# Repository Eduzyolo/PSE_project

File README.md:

# PSE_project
This is the official repo for the PSE project 

# LICENSE
This repo is under CC BY-NC 4.0 license

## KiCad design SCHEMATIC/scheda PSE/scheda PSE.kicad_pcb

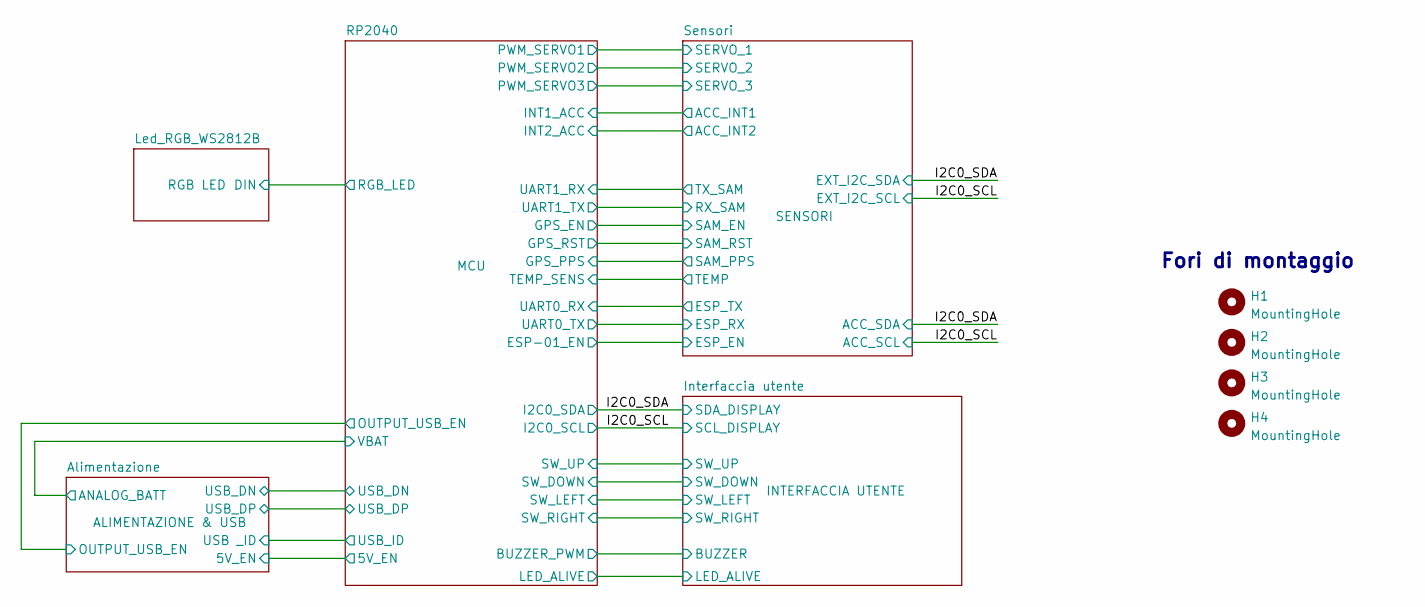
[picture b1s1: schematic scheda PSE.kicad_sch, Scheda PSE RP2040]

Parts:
H1, H2, H3, H4: MountingHole; MountingHole_3.2mm_M3_Pad_Via

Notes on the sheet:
Fori di montaggio

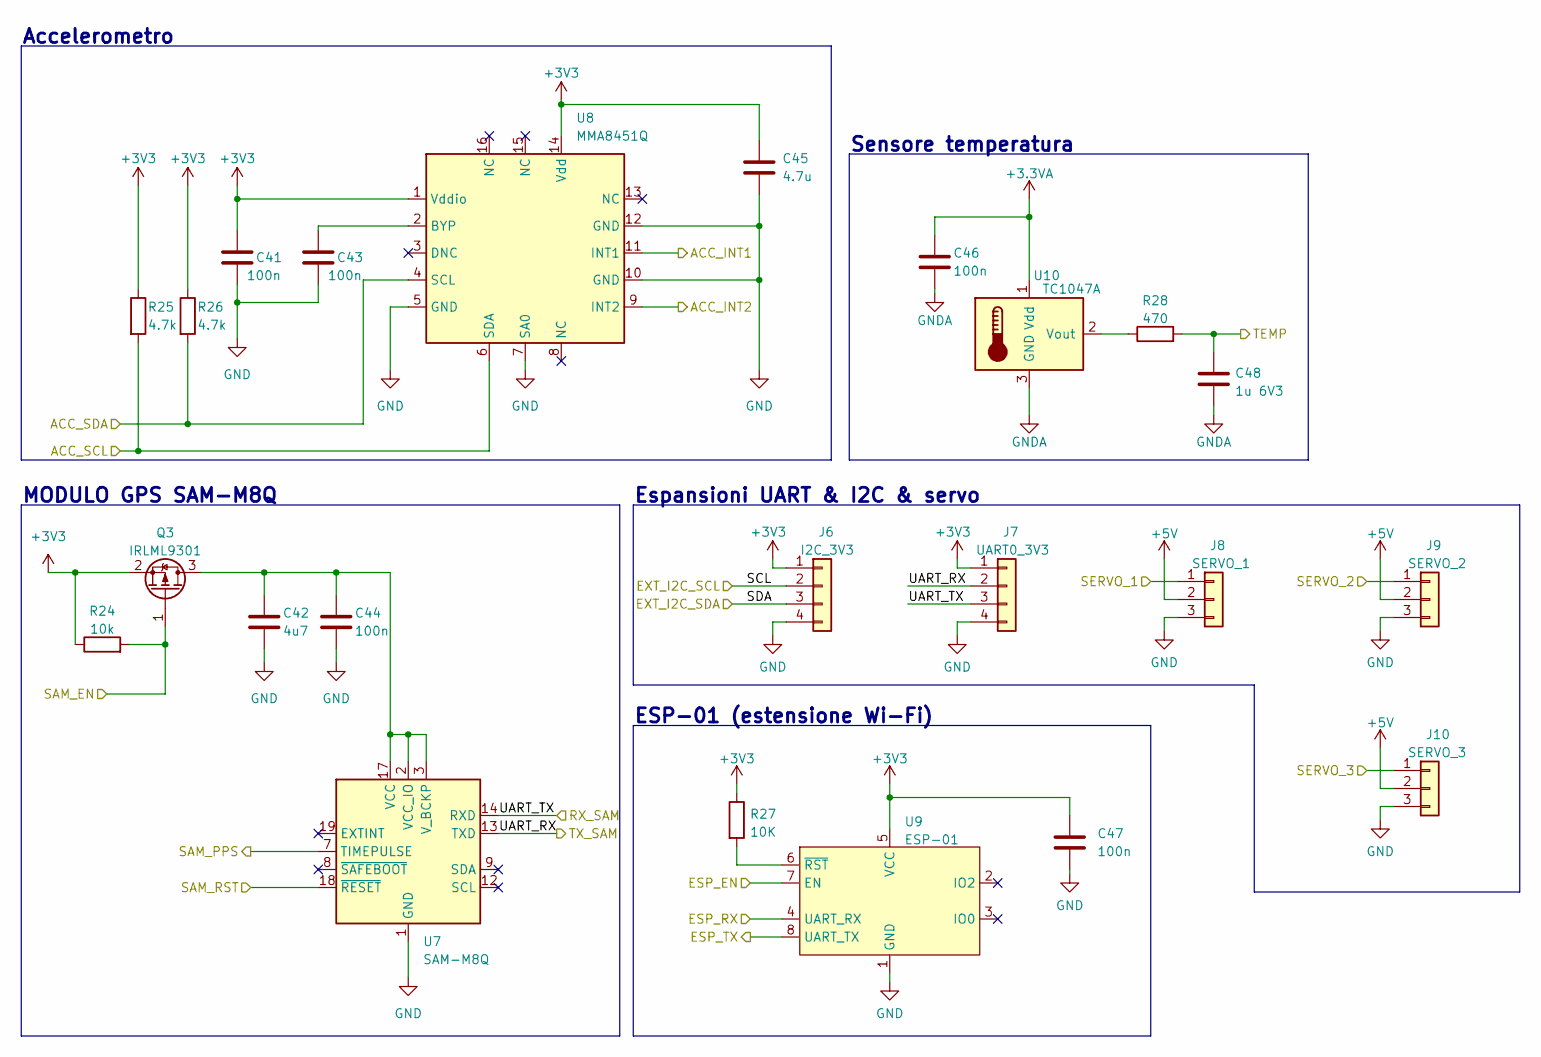
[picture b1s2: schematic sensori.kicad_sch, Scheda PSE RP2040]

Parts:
C41, C43, C44, C46, C47: 100n; C_0603_1608Metric
C42: 4u7; C_0603_1608Metric
C45: 4.7u; C_0603_1608Metric
C48: 1u 6V3; C_0603_1608Metric
J6: I2C_3V3; JST_XH_B4B-XH-A_1x04_P2.50mm_Vertical
J7: UART0_3V3; JST_XH_B4B-XH-A_1x04_P2.50mm_Vertical
J8: SERVO_1; PinHeader_1x03_P2.54mm_Vertical
J9: SERVO_2; PinHeader_1x03_P2.54mm_Vertical
J10: SERVO_3; PinHeader_1x03_P2.54mm_Vertical
Q3: IRLML9301; SOT-23
R24: 10k; R_0603_1608Metric
R25, R26: 4.7k; R_0603_1608Metric
R27: 10K; R_0603_1608Metric
R28: 470; R_0603_1608Metric
U7: SAM-M8Q; SAM_M8Q
U8: MMA8451Q; QFN-16
U9: ESP-01
U10: TC1047A; SOT-23

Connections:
+3.3VA: C46.1, U10.1 (Vdd); also elsewhere on the board
+3V3: C41.1, C45.1, C47.1, J6.1, J7.1, Q3.2 (S), R24.1, R25.1, R26.1, R27.1, U8.1 (Vddio), U8.14 (Vdd), U9.5 (VCC); also elsewhere on the board
+5V: J8.2, J9.2, J10.2; also elsewhere on the board
/I2C0_SCL: J6.2, R25.2, U8.6 (SDA); also elsewhere on the board
/I2C0_SDA: J6.3, R26.2, U8.4 (SCL); also elsewhere on the board
/RP2040/ESP-01_EN: U9.7 (EN); also elsewhere on the board
/RP2040/GPS_EN: Q3.1 (G), R24.2; also elsewhere on the board
/RP2040/GPS_PPS: U7.7 (TIMEPULSE); also elsewhere on the board
/RP2040/GPS_RST: U7.18 (~RESET); also elsewhere on the board
/RP2040/INT1_ACC: U8.11 (INT1); also elsewhere on the board
/RP2040/INT2_ACC: U8.9 (INT2); also elsewhere on the board
/RP2040/PWM_SERVO1: J8.1; also elsewhere on the board
/RP2040/PWM_SERVO2: J9.1; also elsewhere on the board
/RP2040/PWM_SERVO3: J10.1; also elsewhere on the board
/RP2040/TEMP_SENS: C48.1, R28.2; also elsewhere on the board
/RP2040/UART0_RX: U9.8 (UART_TX); also elsewhere on the board
/RP2040/UART0_TX: U9.4 (UART_RX); also elsewhere on the board
/Sensori/UART_RX: J7.2, U7.13 (TXD); also elsewhere on the board
/Sensori/UART_TX: J7.3, U7.14 (RXD); also elsewhere on the board
GND: C41.2, C42.2, C43.2, C44.2, C45.2, C47.2, J6.4, J7.4, J8.3, J9.3, J10.3, U7.1 (GND), U7.4 (GND), U7.5 (GND), U7.6 (GND), U7.10 (GND), U7.11 (GND), U7.15 (GND), U7.16 (GND), U7.20 (GND), U8.5 (GND), U8.7 (SA0), U8.10 (GND), U8.12 (GND), U9.1 (GND); also elsewhere on the board
GNDA: C46.2, C48.2, U10.3 (GND); also elsewhere on the board
unnamed: C42.1, C44.1, Q3.3 (D), U7.2 (VCC_IO), U7.3 (V_BCKP), U7.17 (VCC)
unnamed: C43.1, U8.2 (BYP)
unnamed: R27.2, U9.6 (~RST)
unnamed: R28.1, U10.2 (Vout)

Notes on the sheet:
MODULO GPS SAM-M8Q
Accelerometro
Espansioni UART & I2C & servo
ESP-01 (estensione Wi-Fi)
Sensore temperatura

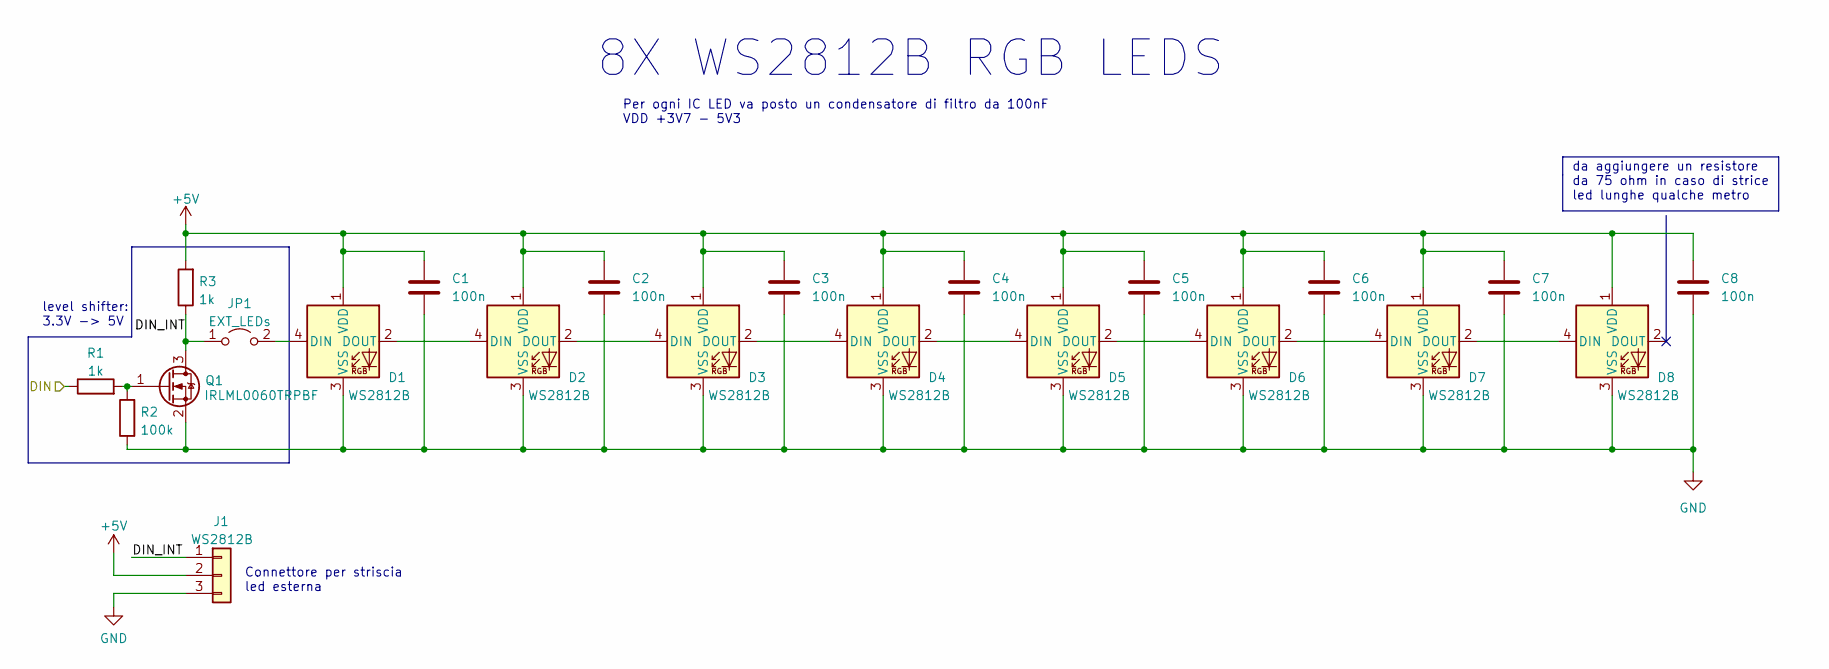
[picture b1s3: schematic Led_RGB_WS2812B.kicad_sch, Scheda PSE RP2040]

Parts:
C1, C2, C3, C4, C5, C6, C7, C8: 100n; C_0603_1608Metric
D1, D2, D3, D4, D5, D6, D7, D8: WS2812B; LED_WS2812B_PLCC4_5.0x5.0mm_P3.2mm
J1: WS2812B; JST_XH_B3B-XH-A_1x03_P2.50mm_Vertical
JP1: EXT_LEDs; PinHeader_1x02_P2.54mm_Vertical
Q1: IRLML0060TRPBF; SOT-23
R1, R3: 1k; R_0603_1608Metric
R2: 100k; R_0603_1608Metric

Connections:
+5V: C1.1, C2.1, C3.1, C4.1, C5.1, C6.1, C7.1, C8.1, D1.1 (VDD), D2.1 (VDD), D3.1 (VDD), D4.1 (VDD), D5.1 (VDD), D6.1 (VDD), D7.1 (VDD), D8.1 (VDD), J1.2, R3.2; also elsewhere on the board
/Led_RGB_WS2812B/DIN: R1.1; also elsewhere on the board
/Led_RGB_WS2812B/DIN_INT: J1.1, JP1.1 (A), Q1.3 (D), R3.1
GND: C1.2, C2.2, C3.2, C4.2, C5.2, C6.2, C7.2, C8.2, D1.3 (VSS), D2.3 (VSS), D3.3 (VSS), D4.3 (VSS), D5.3 (VSS), D6.3 (VSS), D7.3 (VSS), D8.3 (VSS), J1.3, Q1.2 (S), R2.1; also elsewhere on the board
unnamed: D1.2 (DOUT), D2.4 (DIN)
unnamed: D1.4 (DIN), JP1.2 (B)
unnamed: D2.2 (DOUT), D3.4 (DIN)
unnamed: D3.2 (DOUT), D4.4 (DIN)
unnamed: D4.2 (DOUT), D5.4 (DIN)
unnamed: D5.2 (DOUT), D6.4 (DIN)
unnamed: D6.2 (DOUT), D7.4 (DIN)
unnamed: D7.2 (DOUT), D8.4 (DIN)
unnamed: Q1.1 (G), R1.2, R2.2

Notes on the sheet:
Per ogni IC LED va posto un condensatore di filtro da 100nF VDD +3V7 - 5V3
Connettore per striscia led esterna
da aggiungere un resistore da 75 ohm in caso di strice led lunghe qualche metro
level shifter: 3.3V -> 5V
8X WS2812B RGB LEDS

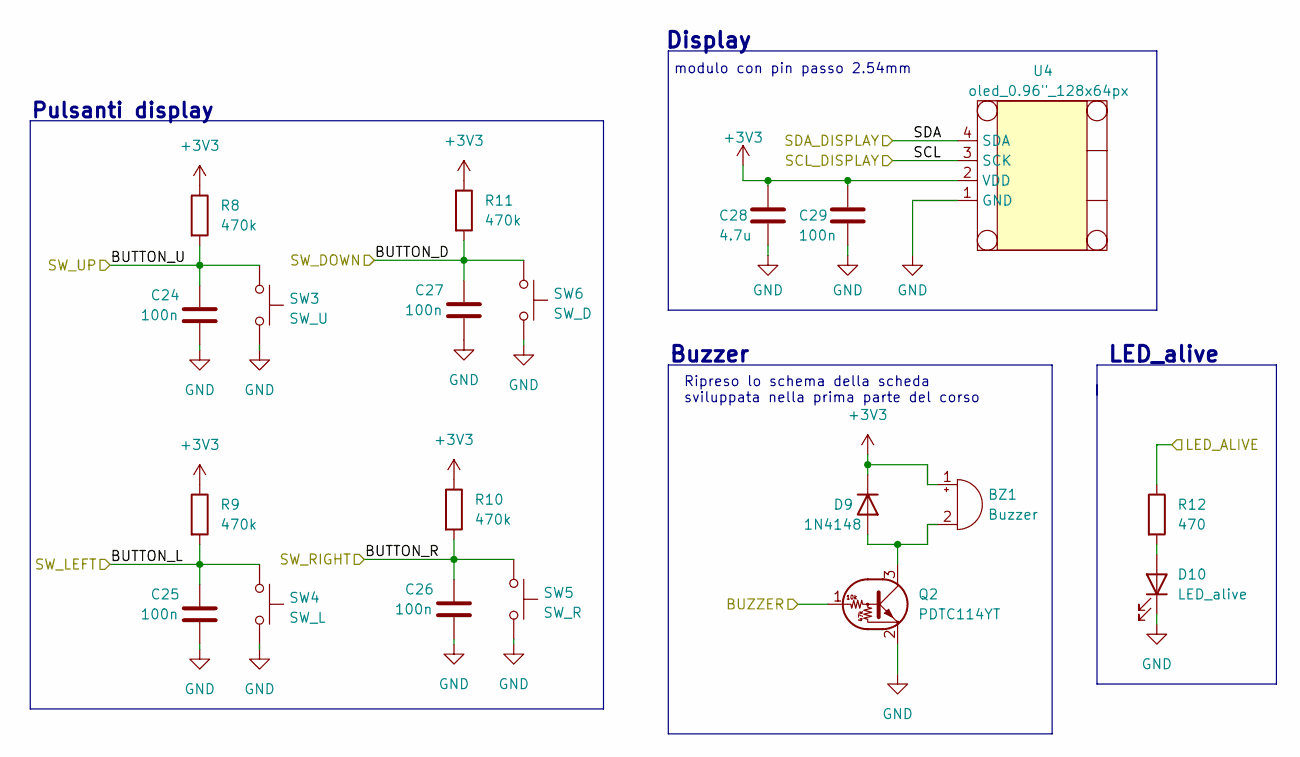
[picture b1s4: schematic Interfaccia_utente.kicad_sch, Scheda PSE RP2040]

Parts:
BZ1: Buzzer; MLT-8530
C24, C25, C26, C27, C29: 100n; C_0603_1608Metric
C28: 4.7u; C_0603_1608Metric
D9: 1N4148; D_SOD-123
D10: LED_alive; LED_0603_1608Metric
Q2: PDTC114YT; SOT-23
R8, R9, R10, R11: 470k; R_0603_1608Metric
R12: 470; R_0603_1608Metric
SW3: SW_U; SW_SPST_EVQP0
SW4: SW_L; SW_SPST_EVQP0
SW5: SW_R; SW_SPST_EVQP0
SW6: SW_D; SW_SPST_EVQP0
U4: oled_0.96"_128x64px; 128x64OLED

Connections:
+3V3: BZ1.1 (-), C28.1, C29.1, D9.1 (K), R8.1, R9.1, R10.1, R11.1, U4.2 (VDD); also elsewhere on the board
/I2C0_SCL: U4.3 (SCK); also elsewhere on the board
/I2C0_SDA: U4.4 (SDA); also elsewhere on the board
/Interfaccia utente/BUTTON_D: C27.1, R11.2, SW6.1; also elsewhere on the board
/Interfaccia utente/BUTTON_L: C25.1, R9.2, SW4.2; also elsewhere on the board
/Interfaccia utente/BUTTON_R: C26.1, R10.2, SW5.2; also elsewhere on the board
/Interfaccia utente/BUTTON_U: C24.1, R8.2, SW3.2; also elsewhere on the board
/Interfaccia utente/BUZZER: Q2.1 (B); also elsewhere on the board
/Interfaccia utente/LED_ALIVE: R12.1; also elsewhere on the board
GND: C24.2, C25.2, C26.2, C27.2, C28.2, C29.2, D10.1 (K), Q2.2 (E), SW3.1, SW4.1, SW5.1, SW6.2, U4.1 (GND); also elsewhere on the board
unnamed: BZ1.2 (+), D9.2 (A), Q2.3 (C)
unnamed: D10.2 (A), R12.2

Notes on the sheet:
Display
modulo con pin passo 2.54mm
Buzzer
LED_alive
Pulsanti display
Ripreso lo schema della scheda sviluppata nella prima parte del corso

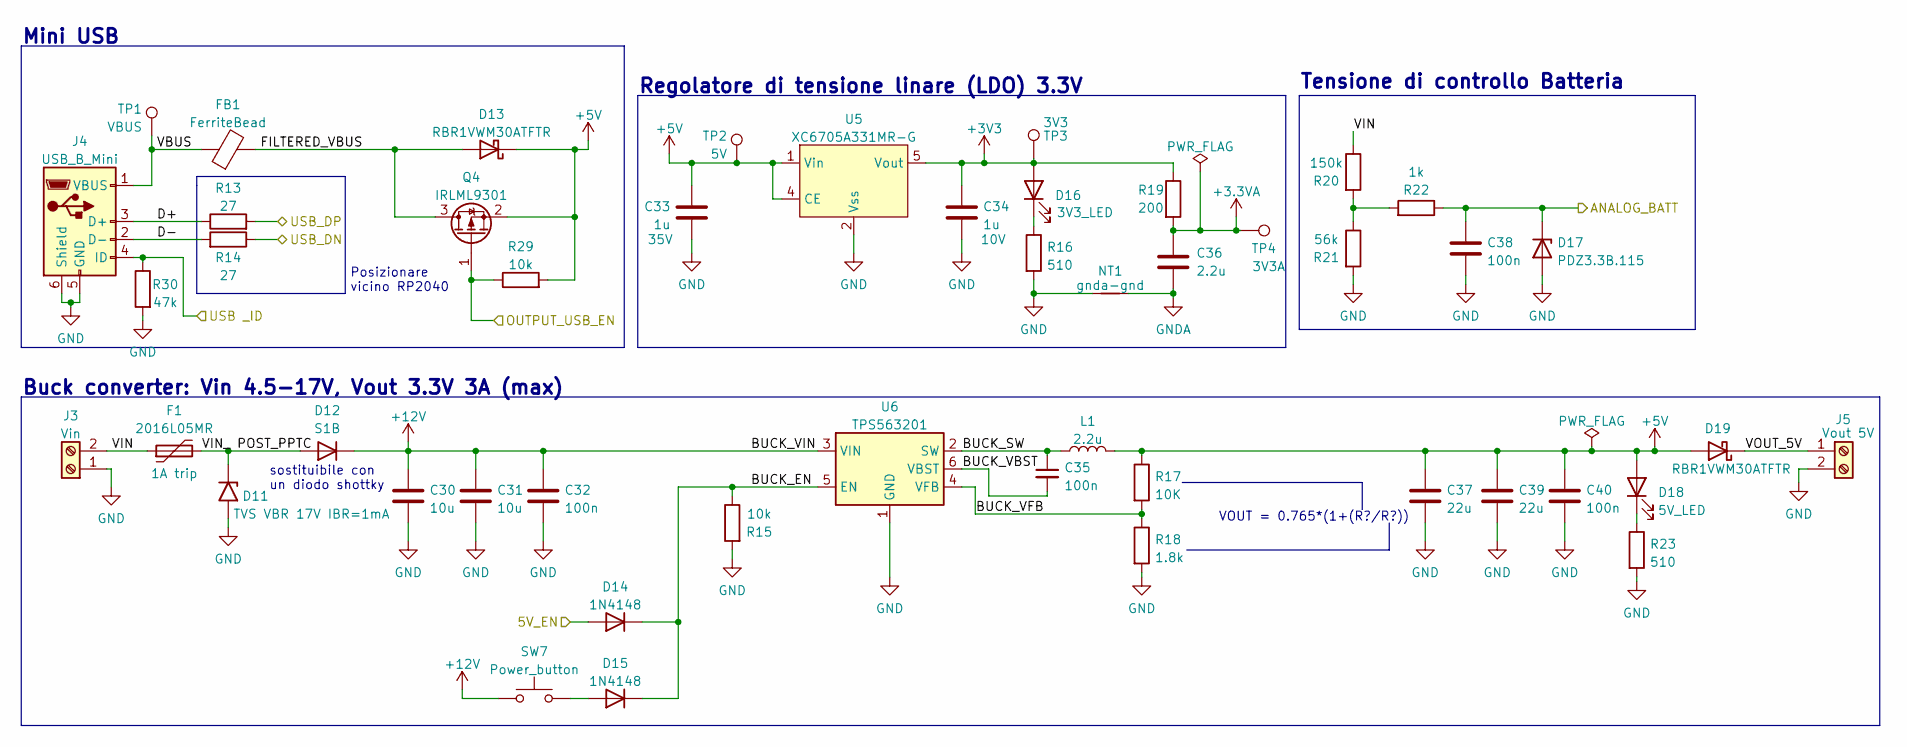
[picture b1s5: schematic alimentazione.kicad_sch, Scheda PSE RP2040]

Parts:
C30, C31: 10u; C_0805_2012Metric
C32, C35, C38, C40: 100n; C_0603_1608Metric
C33: 1u; C_0603_1608Metric; Voltage 35V
C34: 1u; C_0603_1608Metric; Voltage 10V
C36: 2.2u; C_0603_1608Metric
C37, C39: 22u; C_0805_2012Metric
D11: TVS VBR 17V IBR=1mA; D_SMA; mouser 576-SMAJ15A
D12: S1B; D_SMA; farnell 2675037
D13, D19: RBR1VWM30ATFTR; D_SOD-123; farnell 2311223
D14, D15: 1N4148; D_SOD-123
D16: 3V3_LED; LED_0805_2012Metric
D17: PDZ3.3B.115; D_SOD-323_HandSoldering
D18: 5V_LED; LED_0805_2012Metric
F1: 2016L05MR; Fuse_1206_3216Metric; Rating 1A trip; farnell 1652159
FB1: FerriteBead; C_0805_2012Metric; farnell 1515661
J3: Vin; TerminalBlock_bornier-2_P5.08mm
J4: USB_B_Mini; USB mini
J5: Vout 5V; TerminalBlock_bornier-2_P5.08mm
L1: 2.2u; IHLP1212BZER2R2M11; farnell 2056527
NT1: gnda-gnd; NetTie-2_SMD_Pad0.5mm
Q4: IRLML9301; SOT-23
R13, R14: 27; R_0603_1608Metric
R15, R29: 10k; R_0603_1608Metric
R16, R23: 510; R_0603_1608Metric
R17: 10K; R_0603_1608Metric
R18: 1.8k; R_0603_1608Metric
R19: 200; R_0603_1608Metric
R20: 150k; R_0603_1608Metric
R21: 56k; R_0603_1608Metric
R22: 1k; R_0603_1608Metric
R30: 47k; R_0603_1608Metric
SW7: Power_button; SW_SPST_EVQP0
TP1: VBUS; TestPoint_THTPad_D1.5mm_Drill0.7mm
TP2: 5V; TestPoint_THTPad_D1.5mm_Drill0.7mm
TP3: 3V3; TestPoint_THTPad_D1.5mm_Drill0.7mm
TP4: 3V3A; TestPoint_THTPad_D1.5mm_Drill0.7mm
U5: XC6705A331MR-G; SOT-23-5; farnell 4144775
U6: TPS563201; SOT-23-6

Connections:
+3.3VA: C36.1, R19.2, TP4.1; also elsewhere on the board
+3V3: C34.1, D16.2 (A), R19.1, TP3.1, U5.5 (Vout); also elsewhere on the board
+5V: C33.1, C37.1, C39.1, C40.1, D13.1 (K), D18.2 (A), D19.2 (A), L1.2, Q4.2 (S), R17.1, R29.2, TP2.1, U5.1 (Vin), U5.4 (CE); also elsewhere on the board
+12V: C30.1, C31.1, C32.1, D12.1 (K), SW7.1, U6.3 (VIN)
/Alimentazione/5V_EN: D14.2 (A); also elsewhere on the board
/Alimentazione/ANALOG_BATT: C38.1, D17.1 (K), R22.1; also elsewhere on the board
/Alimentazione/BUCK_EN: D14.1 (K), D15.1 (K), R15.1, U6.5 (EN)
/Alimentazione/BUCK_SW: C35.1, L1.1, U6.2 (SW)
/Alimentazione/BUCK_VBST: C35.2, U6.6 (VBST)
/Alimentazione/BUCK_VFB: R17.2, R18.1, U6.4 (VFB)
/Alimentazione/D+: J4.3 (D+), R13.1
/Alimentazione/D-: J4.2 (D-), R14.2
/Alimentazione/FILTERED_VBUS: D13.2 (A), FB1.2, Q4.3 (D)
/Alimentazione/OUTPUT_USB_EN: Q4.1 (G), R29.1; also elsewhere on the board
/Alimentazione/USB _ID: J4.4 (ID), R30.1; also elsewhere on the board
/Alimentazione/USB_DN: R14.1; also elsewhere on the board
/Alimentazione/USB_DP: R13.2; also elsewhere on the board
/Alimentazione/VBUS: FB1.1, J4.1 (VBUS), TP1.1
/Alimentazione/VIN: F1.1, J3.2, R20.1
/Alimentazione/VIN_ POST_PPTC: D11.1 (A1), D12.2 (A), F1.2
/Alimentazione/VOUT_5V: D19.1 (K), J5.1
GND: C30.2, C31.2, C32.2, C33.2, C34.2, C37.2, C38.2, C39.2, C40.2, D11.2 (A2), D17.2 (A), J3.1, J4.5 (GND), J4.6 (Shield), J5.2, NT1.1, R15.2, R16.2, R18.2, R21.2, R23.2, R30.2, U5.2 (Vss), U6.1 (GND); also elsewhere on the board
GNDA: C36.2, NT1.2; also elsewhere on the board
unnamed: D15.2 (A), SW7.2
unnamed: D16.1 (K), R16.1
unnamed: D18.1 (K), R23.1
unnamed: R20.2, R21.1, R22.2

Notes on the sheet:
Tensione di controllo Batteria
Posizionare vicino RP2040
sostituibile con un diodo shottky
Buck converter: Vin 4.5-17V, Vout 3.3V 3A (max)
VOUT = 0.765*(1+(R?/R?))
Regolatore di tensione linare (LDO) 3.3V
Mini USB

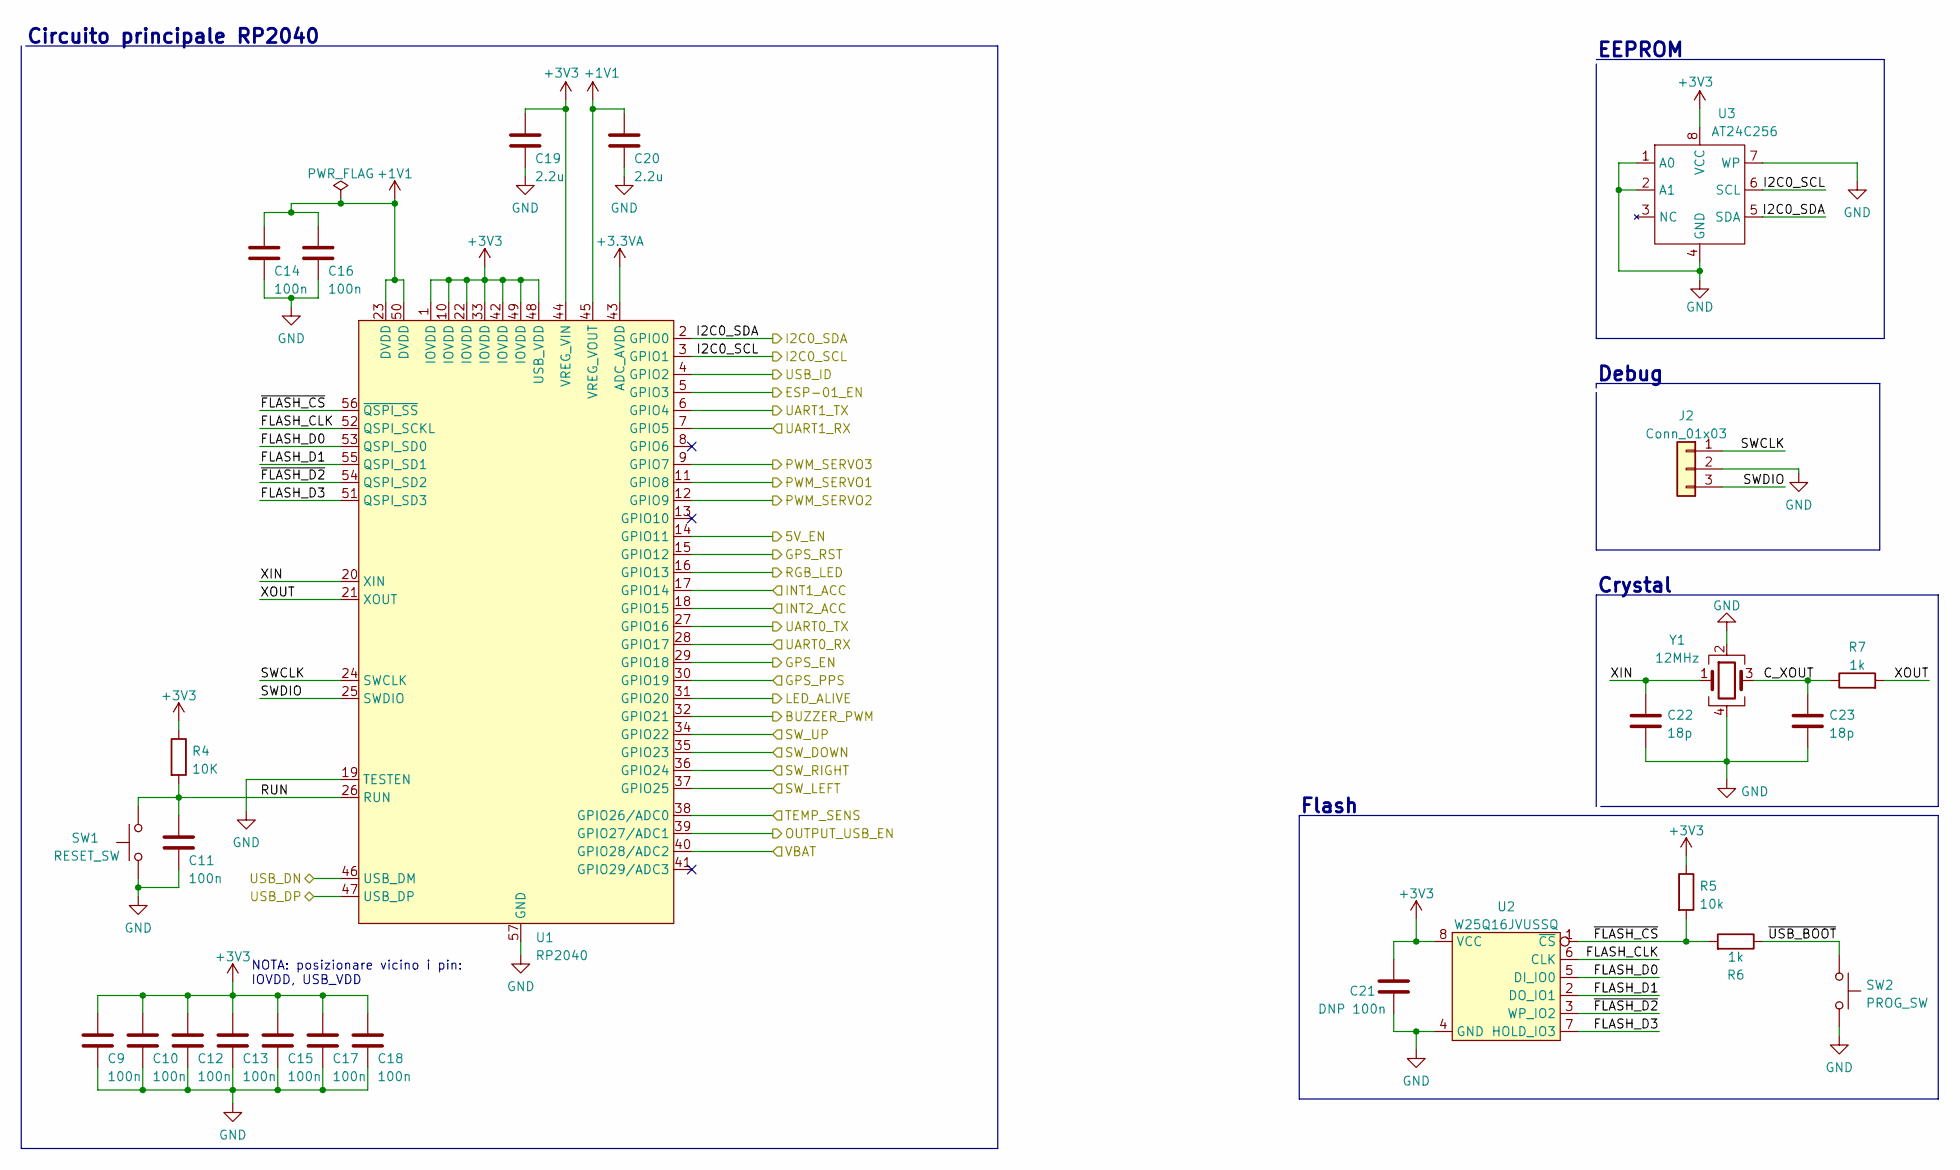
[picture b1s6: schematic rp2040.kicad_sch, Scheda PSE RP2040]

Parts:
C9, C10, C11, C12, C13, C14, C15, C16, C17, C18: 100n; C_0603_1608Metric
C19, C20: 2.2u; C_0603_1608Metric
C21: DNP 100n; C_0603_1608Metric
C22, C23: 18p; C_0603_1608Metric
J2: Conn_01x03; PinHeader_1x03_P2.54mm_Vertical
R4: 10K; R_0603_1608Metric
R5: 10k; R_0603_1608Metric
R6, R7: 1k; R_0603_1608Metric
SW1: RESET_SW; SW_SPST_EVQP0
SW2: PROG_SW; SW_SPST_EVQP0
U1: RP2040; QFN40P700X700X90-57N-D
U2: W25Q16JVUSSQ; SOIC8-150mils
U3: AT24C256; SOIC-8_3.9x4.9mm_P1.27mm
Y1: 12MHz; Crystal_SMD_3225-4Pin_3.2x2.5mm_HandSoldering

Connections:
+1V1: C14.1, C16.1, C20.1, U1.23 (DVDD), U1.45 (VREG_VOUT), U1.50 (DVDD)
+3.3VA: U1.43 (ADC_AVDD); also elsewhere on the board
+3V3: C9.1, C10.1, C12.1, C13.1, C15.1, C17.1, C18.1, C19.1, C21.1, R4.1, R5.1, U1.1 (IOVDD), U1.10 (IOVDD), U1.22 (IOVDD), U1.33 (IOVDD), U1.42 (IOVDD), U1.44 (VREG_VIN), U1.48 (USB_VDD), U1.49 (IOVDD), U2.8 (VCC), U3.8 (VCC); also elsewhere on the board
/Alimentazione/5V_EN: U1.14 (GPIO11); also elsewhere on the board
/Alimentazione/ANALOG_BATT: U1.40 (GPIO28/ADC2); also elsewhere on the board
/Alimentazione/OUTPUT_USB_EN: U1.39 (GPIO27/ADC1); also elsewhere on the board
/Alimentazione/USB _ID: U1.4 (GPIO2); also elsewhere on the board
/Alimentazione/USB_DN: U1.46 (USB_DM); also elsewhere on the board
/Alimentazione/USB_DP: U1.47 (USB_DP); also elsewhere on the board
/I2C0_SCL: U1.3 (GPIO1), U3.6 (SCL); also elsewhere on the board
/I2C0_SDA: U1.2 (GPIO0), U3.5 (SDA); also elsewhere on the board
/Interfaccia utente/BUTTON_D: U1.35 (GPIO23); also elsewhere on the board
/Interfaccia utente/BUTTON_L: U1.37 (GPIO25); also elsewhere on the board
/Interfaccia utente/BUTTON_R: U1.36 (GPIO24); also elsewhere on the board
/Interfaccia utente/BUTTON_U: U1.34 (GPIO22); also elsewhere on the board
/Interfaccia utente/BUZZER: U1.32 (GPIO21); also elsewhere on the board
/Interfaccia utente/LED_ALIVE: U1.31 (GPIO20); also elsewhere on the board
/Led_RGB_WS2812B/DIN: U1.16 (GPIO13); also elsewhere on the board
/RP2040/C_XOUT: C23.1, R7.1, Y1.3
/RP2040/ESP-01_EN: U1.5 (GPIO3); also elsewhere on the board
/RP2040/FLASH_CLK: U1.52 (QSPI_SCKL), U2.6 (CLK)
/RP2040/FLASH_D0: U1.53 (QSPI_SD0), U2.5 (DI_IO0)
/RP2040/FLASH_D1: U1.55 (QSPI_SD1), U2.2 (DO_IO1)
/RP2040/FLASH_D3: U1.51 (QSPI_SD3), U2.7 (HOLD_IO3)
/RP2040/GPS_EN: U1.29 (GPIO18); also elsewhere on the board
/RP2040/GPS_PPS: U1.30 (GPIO19); also elsewhere on the board
/RP2040/GPS_RST: U1.15 (GPIO12); also elsewhere on the board
/RP2040/INT1_ACC: U1.17 (GPIO14); also elsewhere on the board
/RP2040/INT2_ACC: U1.18 (GPIO15); also elsewhere on the board
/RP2040/PWM_SERVO1: U1.11 (GPIO8); also elsewhere on the board
/RP2040/PWM_SERVO2: U1.12 (GPIO9); also elsewhere on the board
/RP2040/PWM_SERVO3: U1.9 (GPIO7); also elsewhere on the board
/RP2040/RUN: C11.1, R4.2, SW1.2, U1.26 (RUN)
/RP2040/SWCLK: J2.1, U1.24 (SWCLK)
/RP2040/SWDIO: J2.3, U1.25 (SWDIO)
/RP2040/TEMP_SENS: U1.38 (GPIO26/ADC0); also elsewhere on the board
/RP2040/UART0_RX: U1.28 (GPIO17); also elsewhere on the board
/RP2040/UART0_TX: U1.27 (GPIO16); also elsewhere on the board
/RP2040/XIN: C22.1, U1.20 (XIN), Y1.1
/RP2040/XOUT: R7.2, U1.21 (XOUT)
/RP2040/~FLASH_CS: R5.2, R6.2, U1.56 (~QSPI_SS), U2.1 (~CS)
/RP2040/~FLASH_D2: U1.54 (QSPI_SD2), U2.3 (WP_IO2)
/RP2040/~USB_BOOT: R6.1, SW2.1
/Sensori/UART_RX: U1.7 (GPIO5); also elsewhere on the board
/Sensori/UART_TX: U1.6 (GPIO4); also elsewhere on the board
GND: C9.2, C10.2, C11.2, C12.2, C13.2, C14.2, C15.2, C16.2, C17.2, C18.2, C19.2, C20.2, C21.2, C22.2, C23.2, J2.2, SW1.1, SW2.2, U1.19 (TESTEN), U1.57 (GND), U2.4 (GND), U3.1 (A0), U3.2 (A1), U3.4 (GND), U3.7 (WP), Y1.2, Y1.4; also elsewhere on the board

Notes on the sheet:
EEPROM
Crystal
Circuito principale RP2040
NOTA: posizionare vicino i pin: IOVDD, USB_VDD
Flash
Debug

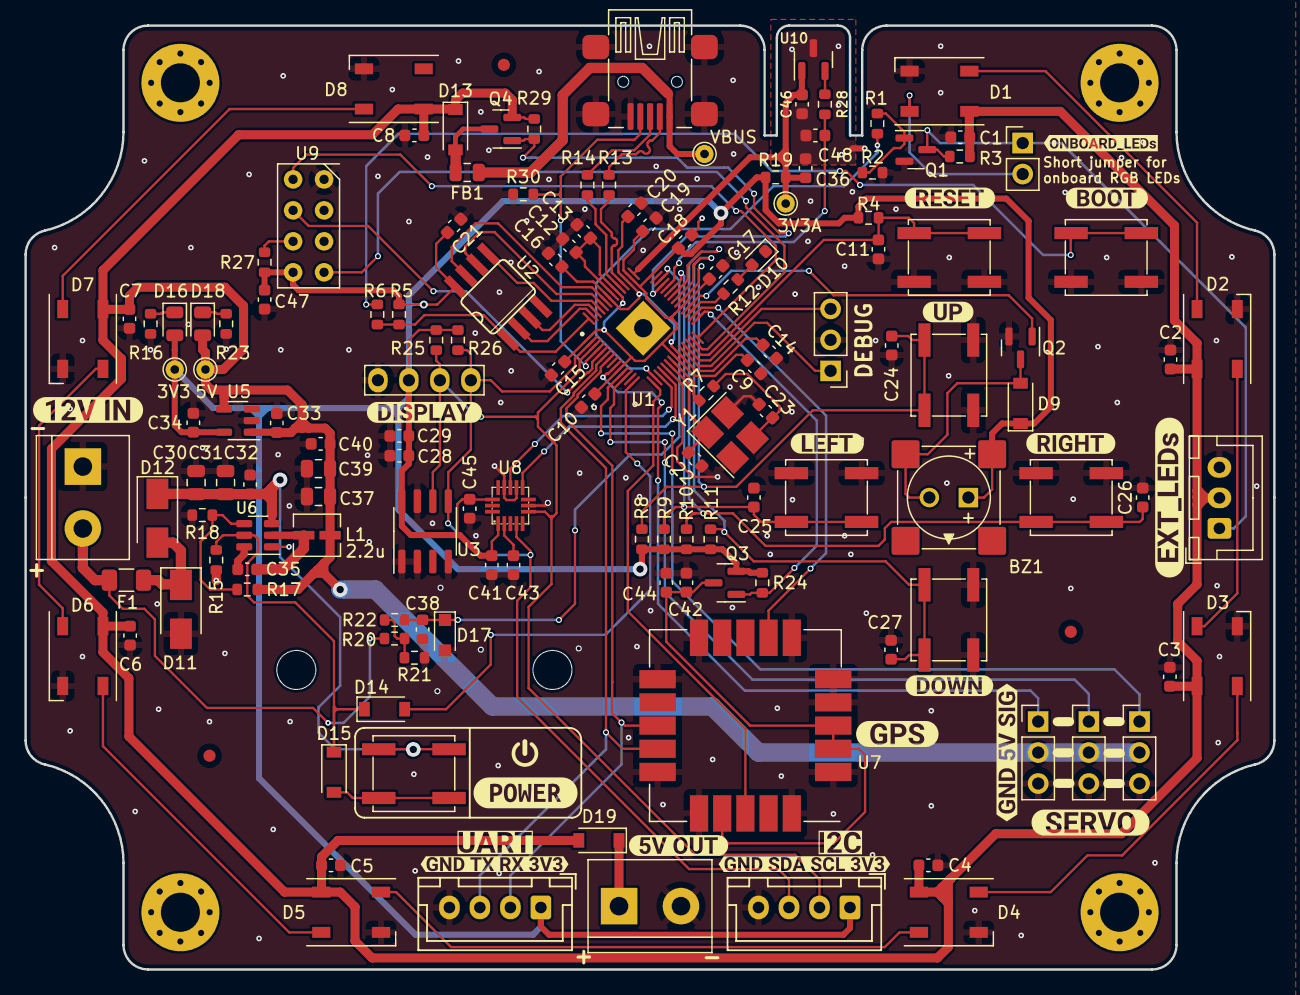
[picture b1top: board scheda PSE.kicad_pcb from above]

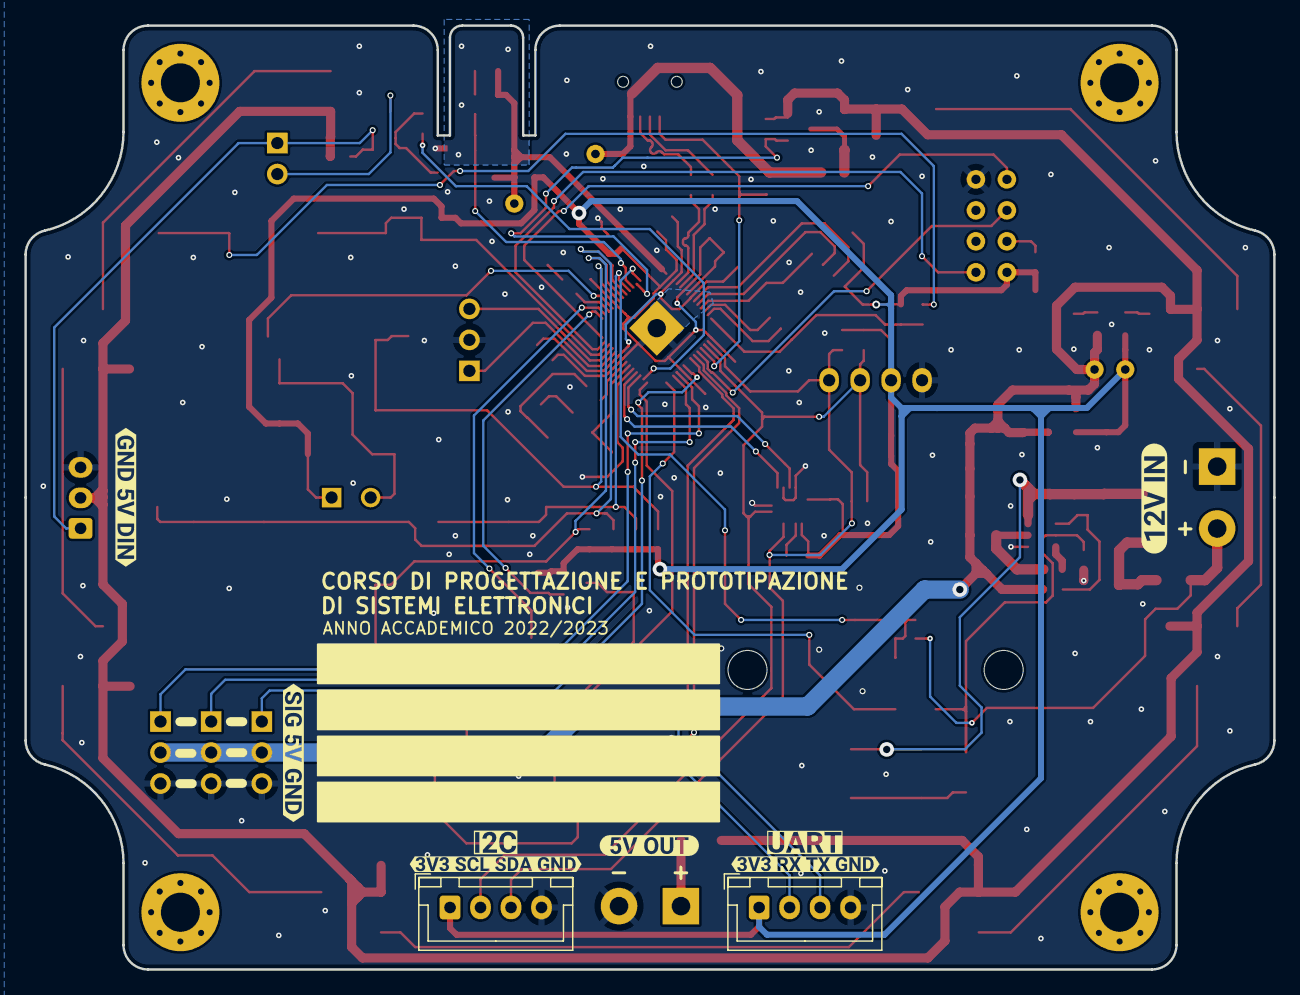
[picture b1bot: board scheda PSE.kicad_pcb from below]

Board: 2 copper layers, 102.4 x 77.4 mm, 170 parts (10 on the bottom side), 80 nets.

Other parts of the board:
kibuzzard-643CF7B7, kibuzzard-643CF7B7#2: G***; kibuzzard-643CF7B7
kibuzzard-643CF7E4: G***; kibuzzard-643CF7E4
kibuzzard-643CF8F2: G***; kibuzzard-643CF8F2
kibuzzard-643CF9A0: G***; kibuzzard-643CF9A0
kibuzzard-643CF9B2: G***; kibuzzard-643CF9B2
kibuzzard-643CF9C9: G***; kibuzzard-643CF9C9
kibuzzard-643CF80B, kibuzzard-643CF80B#2: G***; kibuzzard-643CF80B
kibuzzard-643CF88B: G***; kibuzzard-643CF88B
kibuzzard-643CF96E: G***; kibuzzard-643CF96E
kibuzzard-643CF430: G***; kibuzzard-643CF430
kibuzzard-643CF710: G***; kibuzzard-643CF710
kibuzzard-643CF960: G***; kibuzzard-643CF960
kibuzzard-643CF993: G***; kibuzzard-643CF993
kibuzzard-643CFA52, kibuzzard-643CFA52#2: G***; kibuzzard-643CFA52
kibuzzard-643CFABC, kibuzzard-643CFABC#2: G***; kibuzzard-643CFABC
kibuzzard-643CFBDA: G***; kibuzzard-643CFBDA
kibuzzard-643D3A9E: G***; kibuzzard-643D3A9E
kibuzzard-643DAACA: G***; kibuzzard-643DAACA
kibuzzard-643E45C8: G***; kibuzzard-643E45C8
kibuzzard-643E45D3: G***; kibuzzard-643E45D3
kibuzzard-643E4714: G***; kibuzzard-643E4714
kibuzzard-643E4784: G***; kibuzzard-643E4784
kibuzzard-644128D0: G***; kibuzzard-644128D0

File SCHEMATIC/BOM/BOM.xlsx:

COMPONENTI SCHEDA PSE RP2040 (SCHEDA SINGOLA)
References | Value | Quantity | Footprint | Farnell code | Mouser code | Datasheet
BZ1 | Buzzer | 1 | _PSE:MLT-8530 |  |  | ~
C1-C18, C24-C27, C29, C32, C35, C38, C40, C41, C43, C44, C46, C47 | 100n | 32 | Capacitor_SMD:C_0603_1608Metric |  |  | ~
C19, C20, C36 | 2.2u | 3 | Capacitor_SMD:C_0603_1608Metric |  |  | ~
C21 | 100n | 1 | Capacitor_SMD:C_0603_1608Metric |  |  | ~
C22, C23 | 18p | 2 | Capacitor_SMD:C_0603_1608Metric |  |  | ~
C28, C45 | 4.7u | 2 | Capacitor_SMD:C_0603_1608Metric |  |  | ~
C30, C31 | 10u | 2 | Capacitor_SMD:C_0805_2012Metric |  |  | ~
C33, C34 | 1u | 2 | Capacitor_SMD:C_0603_1608Metric |  |  | ~
C37, C39 | 22u | 2 | Capacitor_SMD:C_0805_2012Metric |  |  | ~
C42 | 4u7 | 1 | Capacitor_SMD:C_0603_1608Metric |  |  | ~
C48 | 1u 6V3 | 1 | Capacitor_SMD:C_0603_1608Metric |  |  | ~
D1-D8 | WS2812B | 8 | LED_SMD:LED_WS2812B_PLCC4_5.0x5.0mm_P3.2mm |  |  | https://cdn-shop.adafruit.com/datasheets/WS2812B.pdf
D9, D14, D15 | 1N4148 | 3 | Diode_SMD:D_SOD-123 |  |  | https://assets.nexperia.com/documents/data-sheet/1N4148_1N4448.pdf
D10 | LED_alive | 1 | LED_SMD:LED_0603_1608Metric |  |  | ~
D11 | TVS VBR 17V IBR=1mA | 1 | Diode_SMD:D_SMA |  | 576-SMAJ15A | https://www.mouser.it/datasheet/2/240/Littelfuse_TVS_Diode_S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
D12 | S1B | 1 | Diode_SMD:D_SMA | 2675037 |  | https://www.farnell.com/datasheets/2863963.pdf
D13, D19 | RBR1VWM30ATFTR | 2 | Diode_SMD:D_SOD-123 | 2311223 |  | https://4donline.ihs.com/images/VipMasterIC/IC/NEXP/NEXP-S-A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
D16 | 3V3_LED | 1 | LED_SMD:LED_0805_2012Metric |  |  | ~
D17 | PDZ3.3B.115 | 1 | Diode_SMD:D_SOD-323_HandSoldering |  |  | ~
D18 | 5V_LED | 1 | LED_SMD:LED_0805_2012Metric |  |  | ~
F1 | 2016L05MR | 1 | Fuse:Fuse_1206_3216Metric | 1652159 |  | https://www.farnell.com/datasheets/2360307.pdf
FB1 | FerriteBead | 1 | Capacitor_SMD:C_0805_2012Metric | 1515661 |  | https://it.farnell.com/murata/blm21pg221sn1d/ferrite-perlina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
J1 | WS2812B | 1 | Connector_JST:JST_XH_B3B-XH-A_1x03_P2.50mm_Vertical |  |  | ~
J2 | Conn_01x03 | 1 | Connector_PinHeader_2.54mm:PinHeader_1x03_P2.54mm_Vertical |  |  | ~
J3 | Vin | 1 | TerminalBlock:TerminalBlock_bornier-2_P5.08mm |  |  | ~
J4 | USB_B_Mini | 1 | _PSE:USB mini |  |  | ~
J5 | Vout 5V | 1 | TerminalBlock:TerminalBlock_bornier-2_P5.08mm |  |  | ~
J6 | I2C_3V3 | 1 | Connector_JST:JST_XH_B4B-XH-A_1x04_P2.50mm_Vertical |  |  | ~
J7 | UART0_3V3 | 1 | Connector_JST:JST_XH_B4B-XH-A_1x04_P2.50mm_Vertical |  |  | ~
J8 | SERVO_1 | 1 | Connector_PinHeader_2.54mm:PinHeader_1x03_P2.54mm_Vertical |  |  | ~
J9 | SERVO_2 | 1 | Connector_PinHeader_2.54mm:PinHeader_1x03_P2.54mm_Vertical |  |  | ~
J10 | SERVO_3 | 1 | Connector_PinHeader_2.54mm:PinHeader_1x03_P2.54mm_Vertical |  |  | ~
JP1 | EXT_LEDs | 1 | Connector_PinHeader_2.54mm:PinHeader_1x02_P2.54mm_Vertical |  |  | ~
L1 | 2.2u | 1 | _PSE:IHLP1212BZER2R2M11 | 2056527 |  | https://www.farnell.com/datasheets/3707258.pdf
Q1 | IRLML0060TRPBF | 1 | Package_TO_SOT_SMD:SOT-23 |  |  | https://www.farnell.com/datasheets/2332193.pdf
Q2 | PDTC114YT | 1 | Package_TO_SOT_SMD:SOT-23
Q3, Q4 | IRLML9301 | 2 | Package_TO_SOT_SMD:SOT-23 |  |  | https://www.infineon.com/dgdl/irlml9301pbf.pdf?fileId=5546d4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
R1, R3, R6, R7, R22 | 1k | 5 | Resistor_SMD:R_0603_1608Metric |  |  | ~
R2 | 100k | 1 | Resistor_SMD:R_0603_1608Metric |  |  | ~
R4, R17, R27 | 10K | 3 | Resistor_SMD:R_0603_1608Metric |  |  | ~
R5, R15, R24, R29 | 10k | 4 | Resistor_SMD:R_0603_1608Metric |  |  | ~
R8-R11 | 470k | 4 | Resistor_SMD:R_0603_1608Metric |  |  | ~
R12, R28 | 470 | 2 | Resistor_SMD:R_0603_1608Metric |  |  | ~
R13, R14 | 27 | 2 | Resistor_SMD:R_0603_1608Metric |  |  | ~
R16, R23 | 510 | 2 | Resistor_SMD:R_0603_1608Metric |  |  | ~
R18 | 1.8k | 1 | Resistor_SMD:R_0603_1608Metric |  |  | ~
R19 | 200 | 1 | Resistor_SMD:R_0603_1608Metric |  |  | ~
R20 | 150k | 1 | Resistor_SMD:R_0603_1608Metric |  |  | ~
R21 | 56k | 1 | Resistor_SMD:R_0603_1608Metric |  |  | ~
R25, R26 | 4.7k | 2 | Resistor_SMD:R_0603_1608Metric |  |  | ~
R30 | 47k | 1 | Resistor_SMD:R_0603_1608Metric |  |  | ~
SW1 | RESET_SW | 1 | Button_Switch_SMD:SW_SPST_EVQP0 |  |  | ~
SW2 | PROG_SW | 1 | Button_Switch_SMD:SW_SPST_EVQP0 |  |  | ~
SW3 | SW_U | 1 | Button_Switch_SMD:SW_SPST_EVQP0 |  |  | ~
SW4 | SW_L | 1 | Button_Switch_SMD:SW_SPST_EVQP0 |  |  | ~
SW5 | SW_R | 1 | Button_Switch_SMD:SW_SPST_EVQP0 |  |  | ~
SW6 | SW_D | 1 | Button_Switch_SMD:SW_SPST_EVQP0 |  |  | ~
SW7 | Power_button | 1 | Button_Switch_SMD:SW_SPST_EVQP0 |  |  | ~
U1 | RP2040 | 1 | _PSE:QFN40P700X700X90-57N-D
U2 | W25Q16JVUSSQ | 1 | _MIA footprint:SOIC8-150mils
U3 | AT24C256 | 1 | Package_SO:SOIC-8_3.9x4.9mm_P1.27mm
U4 | oled_0.96"_128x64px | 1 | _PSE:128x64OLED
U5 | XC6705A331MR-G | 1 | Package_TO_SOT_SMD:SOT-23-5 | 4144775 |  | https://www.farnell.com/datasheets/3902361.pdf
U6 | TPS563201 | 1 | Package_TO_SOT_SMD:SOT-23-6 |  |  | http://www.ti.com/lit/ds/symlink/tps563200.pdf
U7 | SAM-M8Q | 1 | _PSE:SAM_M8Q |  |  | https://www.u-blox.com/sites/default/files/SAM-M8Q_DataSheet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
U8 | MMA8451Q | 1 | _PSE:QFN-16 |  |  | https://www.nxp.com/docs/en/data-sheet/MMA8451Q.pdf
U9 | ESP-01 | 1 | _PSE:ESP-01
U10 | TC1047A | 1 | Package_TO_SOT_SMD:SOT-23 |  |  | http://ww1.microchip.com/downloads/en/DeviceDoc/21498D.pdf
Y1 | 12MHz | 1 | Crystal:Crystal_SMD_3225-4Pin_3.2x2.5mm_HandSoldering |  |  | ~
COMPONENTI SCHEDA ENCODER MAGNETICO (SCHEDA SINGOLA)
References | Value | Quantity | Footprint | Farnell code | Mouser code | Datasheet
C1 | 100n | 1 | Capacitor_SMD:C_0603_1608Metric |  |  | ~
C2 | 10u | 1 | Connector_PinSocket_2.54mm:PinSocket_1x02_P2.54mm_Vertical |  |  | ~
J1 | Analog OUT | 1 | Connector_JST:JST_XH_B3B-XH-A_1x03_P2.50mm_Vertical |  |  | ~
J2 | I2C OUT | 1 | Connector_JST:JST_XH_B4B-XH-A_1x04_P2.50mm_Vertical |  |  | ~
R1 | 10k | 1 | Resistor_SMD:R_0603_1608Metric |  |  | ~
SW1 | mode sel | 1 | Button_Switch_THT:SW_DIP_SPSTx02_Slide_9.78x7.26mm_W7.62mm_P2.54mm | 2864305 |  | https://www.farnell.com/datasheets/2803214.pdf
U1 | AS5600 | 1 | Package_SO:SOIC-8_3.9x4.9mm_P1.27mm |  |  | https://www.mouser.it/datasheet/2/588/AS5600_DS000365_5_00-1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
